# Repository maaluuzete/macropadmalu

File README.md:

# Malu's Macropad

A compact 6-key programmable macropad built around the Seeed XIAO RP2040, featuring a clean 2×3 key layout, a custom PCB, and a cute 3D-printed case.
In addition to the six mechanical keys, the macropad includes a rotary encoder for intuitive controls (such as volume(my case), scrolling, or zoom) and built-in decorative LEDs for a subtle aesthetic touch.
Designed from scratch as my first full hardware project, this macropad is mainly aimed at programming and competitive programming workflows, with custom macros for VS Code and common coding actions.

---

## Features

- 6 programmable mechanical keys (2×3 layout);
- Seeed XIAO RP2040 microcontroller;
- Custom PCB designed in KiCad;
- Custom 3D-printed case and plate designed in Fusion 360;
- Firmware based on KMK+CircuitPython;
- Rotary encoder for system volume control;
- Designed for programming and competitive programming macros.

---

## Tools & Technologies

| Area              | Tool / Technology |
|-------------------|-------------------|
CAD (Case & Top)   | Fusion 360        |
PCB Design           | KiCad             |
Firmware             | KMK (CircuitPython) |
Programming          | Python            |
Version Control      | Git & GitHub      |
Code Editor          | VS Code           |

---

## Project Preview

### Case Design (Fusion 360)

### PCB & Schematic (KiCad)

---

## Repository Structure
```
├── README.md
├── journal.md
├── firmware/
│ └── main.py
├── pcb/
│ ├──gerbers/
│ ├── macropadmaluu.kicad_pcb
│ ├── macropadmaluu.kicad_pro
│ └── macropadmaluu.kicad_sch
├── case/
│ ├── topmalumacropad.f3d
│ ├── malumacropadstep.f3d
│ ├── tampamalumacropad.step
│ ├── malumacropadcase.step
└── docs/
│ ├── images/
```
---

## Development Log
A detailed development log is available in: ``` journal.md ``` :)

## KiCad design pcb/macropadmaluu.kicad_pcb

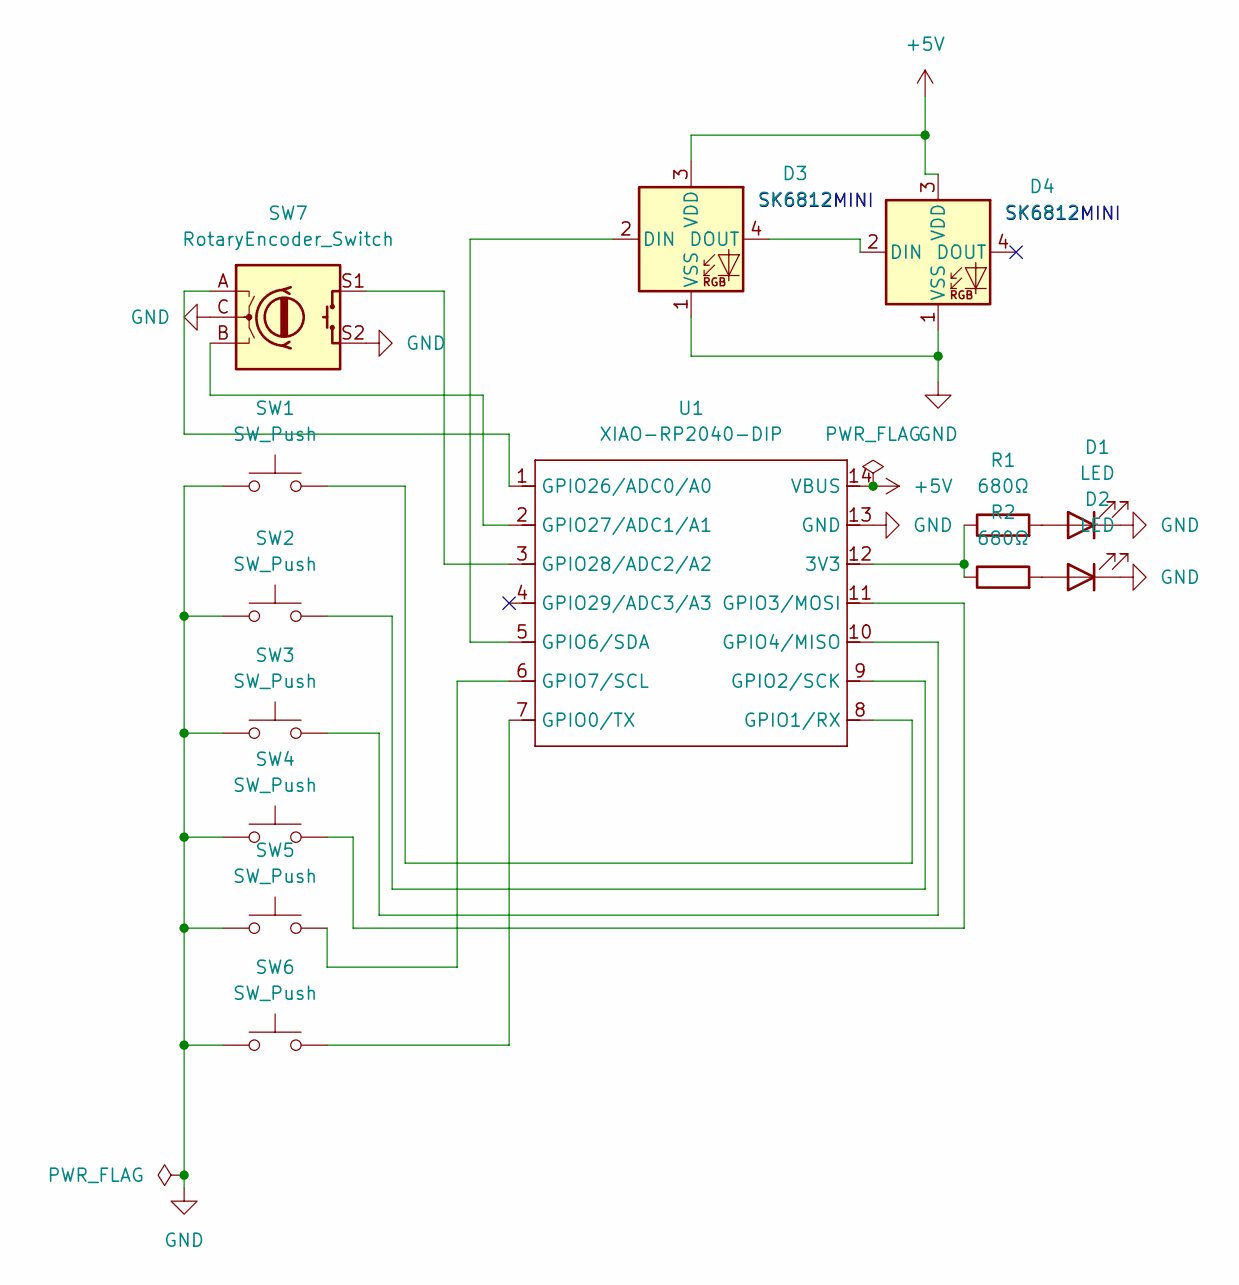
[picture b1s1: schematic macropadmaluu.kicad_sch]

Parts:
D1, D2: LED; LED_D3.0mm
D3, D4: SK6812; LED_SK6812_PLCC4_5.0x5.0mm_P3.2mm
R1, R2: 680Ω; R_Axial_DIN0207_L6.3mm_D2.5mm_P7.62mm_Horizontal
SW1, SW2, SW3, SW4, SW5, SW6: SW_Push; SW_Cherry_MX_1.00u_PCB
SW7: RotaryEncoder_Switch; RotaryEncoder_Alps_EC11E-Switch_Vertical_H20mm
U1: XIAO-RP2040-DIP

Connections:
+5V: D3.3 (VDD), D4.3 (VDD), U1.14 (VBUS)
GND: D1.1 (K), D2.1 (K), D3.1 (VSS), D4.1 (VSS), SW1.1, SW2.1, SW3.1, SW4.1, SW5.1, SW6.1, SW7.C, SW7.S2, U1.13 (GND)
unnamed: D1.2 (A), R1.2
unnamed: D2.2 (A), R2.2
unnamed: D3.2 (DIN), U1.5 (GPIO6/SDA)
unnamed: D3.4 (DOUT), D4.2 (DIN)
unnamed: R1.1, R2.1, U1.12 (3V3)
unnamed: SW6.2, U1.7 (GPIO0/TX)
unnamed: SW1.2, U1.8 (GPIO1/RX)
unnamed: SW2.2, U1.9 (GPIO2/SCK)
unnamed: SW4.2, U1.11 (GPIO3/MOSI)
unnamed: SW3.2, U1.10 (GPIO4/MISO)
unnamed: SW5.2, U1.6 (GPIO7/SCL)
unnamed: SW7.A, U1.1 (GPIO26/ADC0/A0)
unnamed: SW7.B, U1.2 (GPIO27/ADC1/A1)
unnamed: SW7.S1, U1.3 (GPIO28/ADC2/A2)

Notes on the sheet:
SK6812MINI

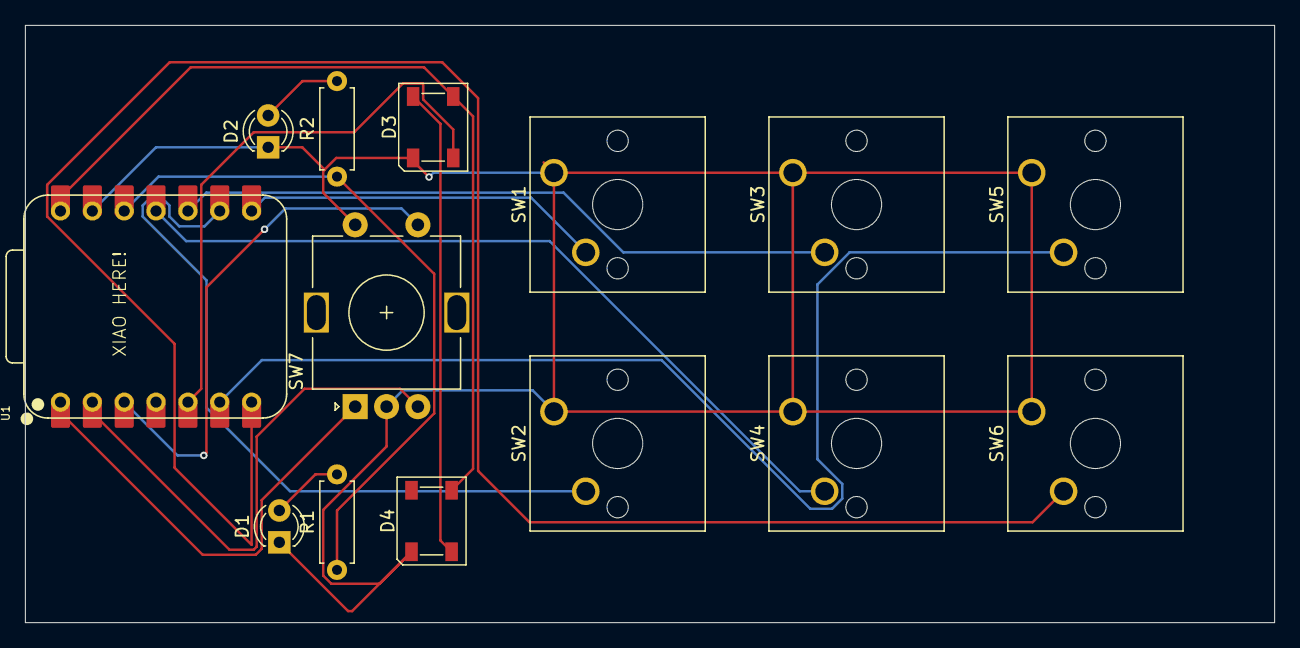
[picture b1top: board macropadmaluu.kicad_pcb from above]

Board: 2 copper layers, 99.6 x 47.6 mm, 14 parts (0 on the bottom side), 16 nets.

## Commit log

2026-01-20 Revise comment on Tinkercad and Fusion access
    Updated the comment about Tinkercad and Fusion access.
2026-01-20 Update journal with macropad project progress
    Added entries for the progress on the macropad project, including the case and lid.
2026-01-20 Initialize KMK keyboard with keymap and macros
2026-01-20 Translate and update project diary entries
    Translated and updated project diary entries from Portuguese to English, enhancing clarity and detail.
2026-01-20 Update README with project details and instructions
    Added detailed project description, features, tools, and instructions.
2026-01-21 Refactor code structure for improved readability and maintainability
2026-01-21 Update README with new file structure for PCB and case
2026-01-21 Remove 'Getting Started' section from README
    Removed the 'Getting Started' section and its instructions from the README.
2026-01-21 Revise README with updated project details
    Updated project description and features for clarity. Added new sections for firmware and manufacturing details.
2026-01-21 Correcting a typo
2026-01-23 Update journal with new project idea
    Added a new entry about changing the project idea to a macropad oscilloscope.
2026-01-24 Revise project diary dates and update project details
    Updated dates in project diary entries to 2026 and added new entries regarding changes in project direction.
2026-01-24 Update development log reference from diary to journal
2026-01-24 Add new entry about project progress
2026-01-24 Add Gerber and drill files for macropadmaluu project
    - Created non-plated through-hole (NPTH) drill file: macropadmaluu-NPTH.drl
    - Created plated through-hole (PTH) drill file: macropadmaluu-PTH.drl
    - Added job file for Gerber generation: macropadmaluu-job.gbrjob
    - All files generated using KiCad version 9.0.6 with appropriate specifications and attributes.
2026-01-24 Revise README with project details and file names
    Updated project description and repository structure details.
2026-01-24 Add rotary encoder for system volume control
2026-01-24 Revise journal entries for clarity and translation
    Updated journal entries to reflect changes in the project scope and progress, translating previous entries from Portuguese to English.

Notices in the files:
README.md:
License: MIT
